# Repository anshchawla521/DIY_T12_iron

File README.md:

# DIY_T12_iron  

This repository conatins all the files for the DIY soldering iron which is compatible with hakko 936 style station and is meant to be used as the replacement PCB for HAKKO 936 style clones. This can support HAKKO T12 irons, HAKKO A1560(hakko 936 station) style irons as well as JBC c245 iron(yet to be checked).  

## Images

## Schematic  

## Code

The original Code was written by [HomeMade Projects](https://www.youtube.com/watch?v=tIUbGNTiDyI). Later i modified it to work with the provided PCB + support for more types of Iron's  

## What did i Learn ?

I learnt that most of the iron's use a triac and are AC powere or if they are DC work only upto 24V because making mosfets work/switch 60V is very hard

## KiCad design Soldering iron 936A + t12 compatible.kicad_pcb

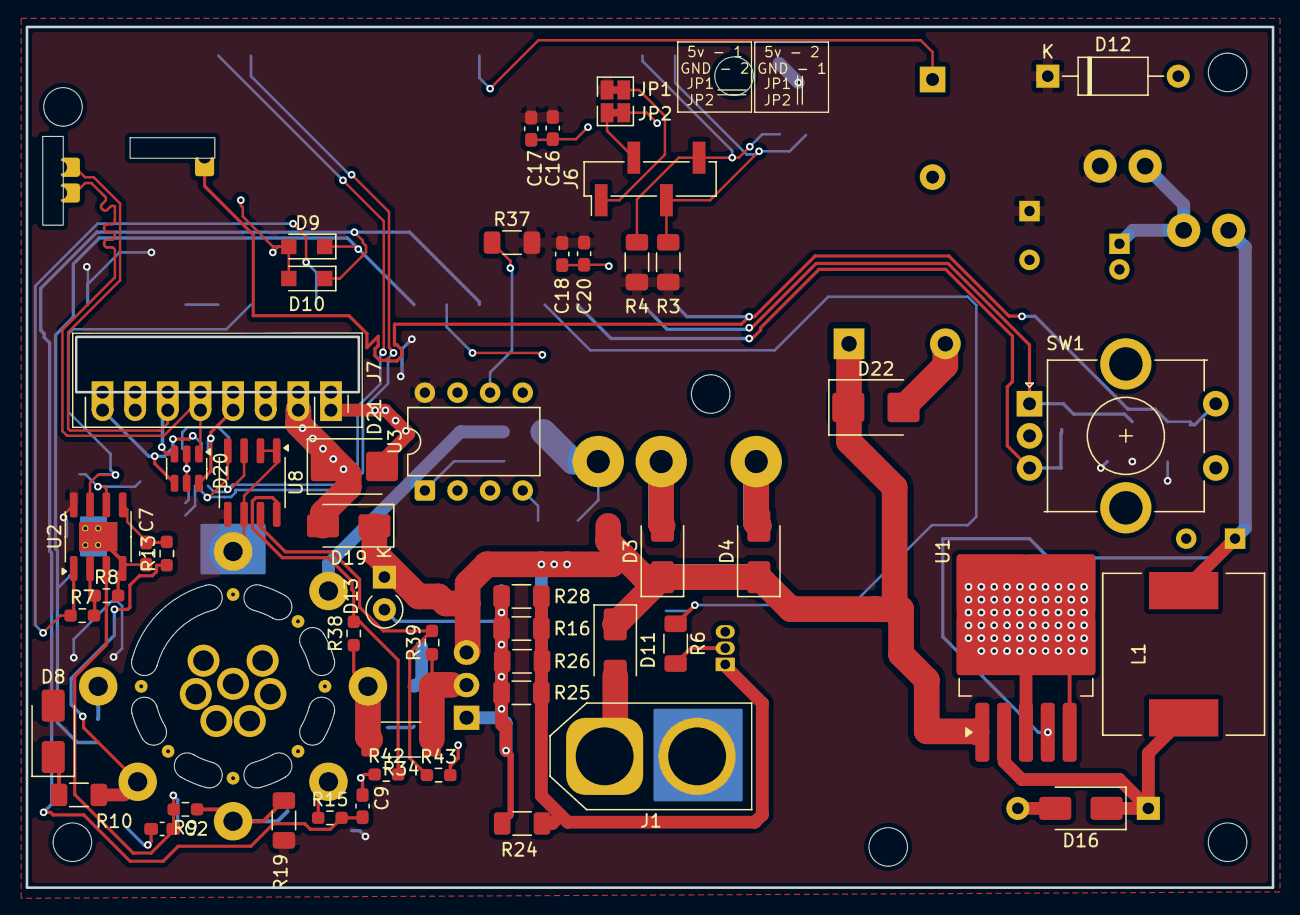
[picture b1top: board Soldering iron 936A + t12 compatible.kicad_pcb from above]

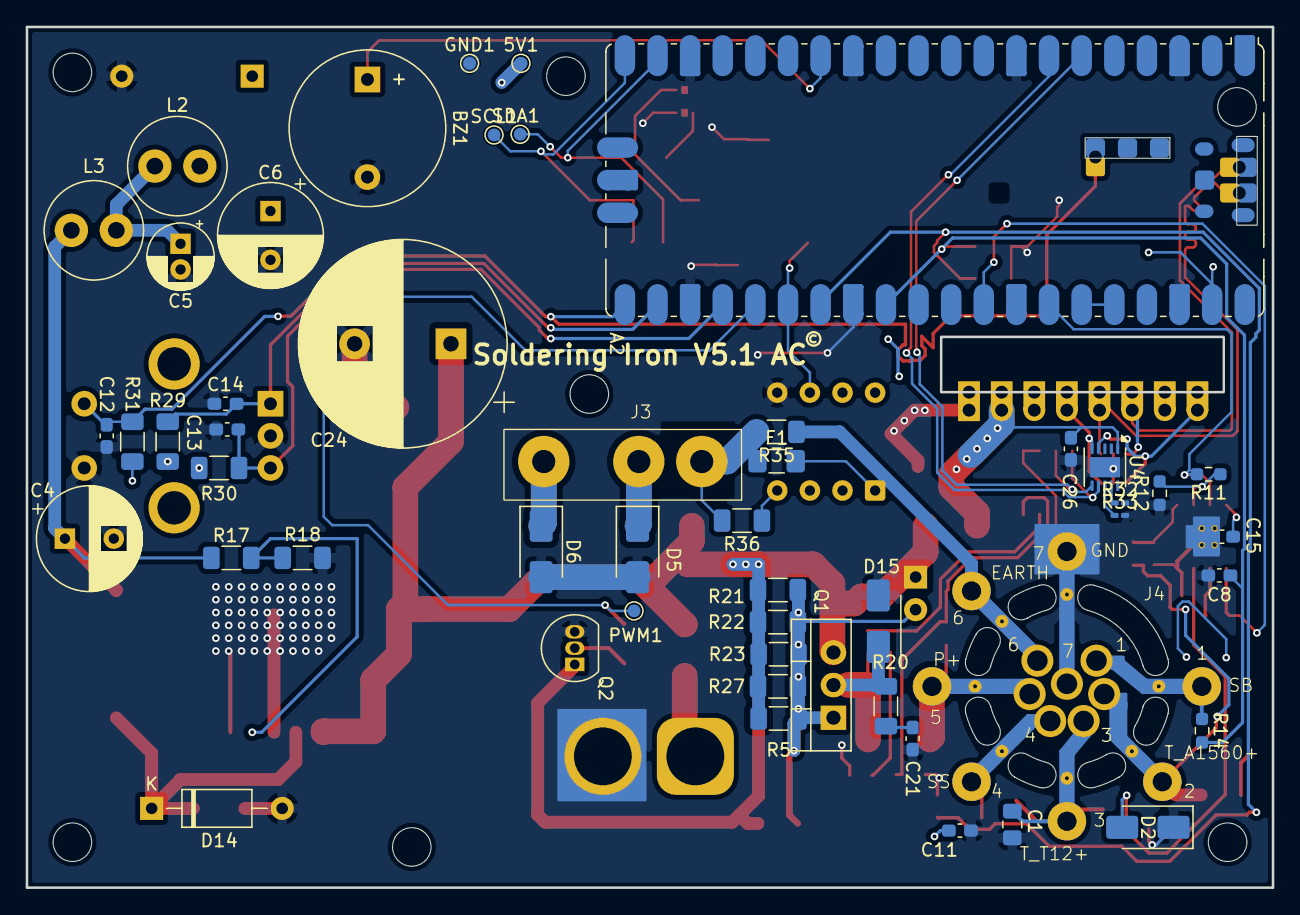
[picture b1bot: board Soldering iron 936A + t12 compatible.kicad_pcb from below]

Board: 2 copper layers, 97.0 x 67.0 mm, 103 parts (51 on the bottom side), 54 nets.

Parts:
5V1: TestPoint; TestPoint_Pad_D1.0mm
A2: RaspberryPi_Pico; RaspberryPi_Pico_SMD
BZ1: Buzzer; Buzzer_12x9.5RM7.6
C1: 0.47uf; C_0805_2012Metric_Pad1.18x1.45mm_HandSolder
C2, C7: 2nf; C_0603_1608Metric_Pad1.08x0.95mm_HandSolder
C4, C6: 220uf; CP_Radial_D8.0mm_P3.80mm
C5: 4.7uF; CP_Radial_D5.0mm_P2.00mm
C8, C9, C11, C12, C13, C14, C15, C16, C17, C18, C20, C21: 100nf; C_0603_1608Metric_Pad1.08x0.95mm_HandSolder
C24: 1000uF; CP_Radial_D16.0mm_P7.50mm
C26: 1uF; C_0603_1608Metric_Pad1.08x0.95mm_HandSolder
D2, D3, D4, D5, D6, D8, D11, D15, D16, D19: SS310; D_SMA
D9, D10: 3.3; Nexperia_CFP3_SOD-123W
D12: 3.3V; D_A-405_P10.16mm_Horizontal
D13: 18V; D_A-405_P2.54mm_Vertical_KathodeUp
D14: 1N5822; D_A-405_P10.16mm_Horizontal
D20: ESDA6V1-5SC6; SOT-23-6
D21: SMBJ24A; D_SMB
D22: SMBJ45A; D_SMB
F1: Fuse; Fuse_1206_3216Metric_Pad1.42x1.75mm_HandSolder
GND1: TestPoint; TestPoint_Pad_D1.0mm
J1: DC INPUT; AMASS_XT60-F_1x02_P7.20mm_Vertical
J3: AC input; BY-G4
J4: output_connector; aviaion_connector
J6: OLED; PinHeader_1x04_P2.54mm_Vertical_SMD_Pin1Left
J7: USB C BREAKOUT BOARD; PinHeader_1x08_P2.54mm_Vertical
JP1, JP2: SolderJumper_2_Bridged; SolderJumper-2_P1.3mm_Bridged_Pad1.0x1.5mm
L1: 33uH; L_12x12mm_H6mm
L2, L3: 100uH; L_Radial_D7.5mm_P3.50mm_Fastron_07P
PWM1: TestPoint; TestPoint_Pad_D1.0mm
Q1: IRF9540N; TO-220-3_Vertical
Q2: BC547; TO-92_Inline
R3, R4, R29, R30, R31, R37: 10k; R_1206_3216Metric_Pad1.30x1.75mm_HandSolder
R5, R21, R22, R23, R27: 1.5k; R_1206_3216Metric_Pad1.30x1.75mm_HandSolder
R6: 2k; R_1206_3216Metric_Pad1.30x1.75mm_HandSolder
R7: 220k; R_0603_1608Metric_Pad0.98x0.95mm_HandSolder
R8, R11, R12: 1k; R_0603_1608Metric_Pad0.98x0.95mm_HandSolder
R9, R13, R14, R15, R38, R39, R42, R43: 10k; R_0603_1608Metric_Pad0.98x0.95mm_HandSolder
R10: 470; R_1206_3216Metric_Pad1.30x1.75mm_HandSolder
R16, R24, R25, R26, R28: 3.3k; R_1206_3216Metric_Pad1.30x1.75mm_HandSolder
R17: 1.7k; R_1206_3216Metric_Pad1.30x1.75mm_HandSolder
R18: 1k; R_1206_3216Metric_Pad1.30x1.75mm_HandSolder
R19: 7.5M; R_1206_3216Metric_Pad1.30x1.75mm_HandSolder
R20: 100; R_1206_3216Metric_Pad1.30x1.75mm_HandSolder
R32: 22.6K; R_0201_0603Metric_Pad0.64x0.40mm_HandSolder
R33: 10k; R_0201_0603Metric_Pad0.64x0.40mm_HandSolder
R34: 0.1; R_2010_5025Metric_Pad1.40x2.65mm_HandSolder
R35: 1M; R_1206_3216Metric_Pad1.30x1.75mm_HandSolder
R36: 50K; R_1206_3216Metric_Pad1.30x1.75mm_HandSolder
SCL1: TestPoint; TestPoint_Pad_D1.0mm
SDA1: TestPoint; TestPoint_Pad_D1.0mm
SW1: RotaryEncoder_Switch; RotaryEncoder_Alps_EC11E-Switch_Vertical_H20mm_CircularMoun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
U1: LM2596S-ADJ; TO-263-5_TabPin3
U2: LM358; SOIC-8-1EP_3.9x4.9mm_P1.27mm_EP2.29x3mm_ThermalVias
U3: HCPL-3700; DIP-8_W7.62mm
U4: HUSB238; DFN-10-1EP_3x3mm_P0.5mm_EP1.58x2.35mm
U8: INA219AxD; SOIC-8_3.9x4.9mm_P1.27mm

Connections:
+3.3V: 5V1.1, A2.39 (VSYS), C6.1, C11.2, C15.1, C16.1, C17.1, C18.1, C20.1, D8.2 (A), D12.1 (K), JP1.1 (A), L2.2, R3.2, R4.2, R19.2, R29.1, R30.1, R31.2, R37.2, U2.8 (V+), U3.8 (VCC), U8.5 (VS)
+3V3: A2.35 (ADC_VREF), A2.36 (3V3)
/3.3v_unfiltered: C4.1, L1.2, L3.1, R17.2
/BUZZER: A2.14 (GPIO10), BZ1.1 (+)
/CC1: D20.6 (IO5), J7.4 (CC1), U4.5 (CC2)
/CC2: D20.4 (IO3), J7.8 (CC2), U4.4 (CC1)
/D+: A2.TP3 (USB_DP), D20.3 (IO2), J7.6 (D+)
/D-: A2.TP2 (USB_DM), D20.1 (IO1), J7.5 (D-)
/ENCODER A: A2.22 (GPIO17), C14.1, R29.2, SW1.A
/ENCODER B: A2.24 (GPIO18), C13.1, R30.2, SW1.B
/ENCODER S: A2.21 (GPIO16), A2.TP6 (~BOOTSEL), C12.1, R31.1, SW1.S2
/LEAK_ERR: A2.26 (GPIO20), R37.1, U3.6 (VO)
/MOS_OUT: D15.1 (K), Q1.2 (D), R20.1, R34.1, R39.1
/P+: J4.5, R34.2, R38.1
/PWM: A2.25 (GPIO19), PWM1.1, R6.1
/SCL: A2.7 (GPIO5), U4.7 (SCL), U8.4 (SCL)
/SCL1: A2.20 (GPIO15), J6.3 (GND), R3.1, SCL1.1
/SDA: A2.6 (GPIO4), U4.6 (SDA), U8.3 (SDA)
/SDA1: A2.19 (GPIO14), J6.4 (VDD), R4.1, SDA1.1
/VIN: C24.1, D3.1 (K), D4.1 (K), D11.1 (K), D13.1 (K), D19.1 (K), D22.1 (A1), Q1.3 (S), R5.1, R21.1, R22.1, R23.1, R27.1, U1.1 (VIN)
/VIN_USBC: C26.1, D19.2 (A), D21.1 (A1), J7.2 (VBUS), U4.1 (V_{DD})
/switch_Boost: J4.1, R14.1
/switch_Boost_d: A2.29 (GPIO22), C8.1, D9.1 (K), R14.2
/switch_sleep: J4.4, R15.1
/switch_sleep_d: A2.27 (GPIO21), C9.1, D10.1 (K), R15.2
/temp_readback_1: A2.32 (GPIO27_ADC1), R7.1, U2.1
/temp_readback_2: A2.34 (GPIO28_ADC2), R11.2, U2.7
/thermocouple_a1560 +: J4.2, R10.1, R13.1
/thermocouple_t12 +: C1.1, J4.3, R9.1, R19.1
Earth: F1.1, J3.1, R35.2, R36.2
GND: A2.3 (GND), A2.8 (GND), A2.13 (GND), A2.18 (GND), A2.23 (GND), A2.28 (GND), A2.38 (GND), A2.D2 (GND), BZ1.2 (-), C1.2, C2.2, C4.2, C5.2, C6.2, C7.2, C8.2, C9.2, C11.1, C12.2, C13.2, C14.2, C15.2, C16.2, C17.2, C18.2, C20.2, C21.2, C24.2, C26.2, D2.1 (K), D5.2 (A), D6.2 (A), D9.2 (A), D10.2 (A), D12.2 (A), D14.2 (A), D15.2 (A), D16.2 (A), D20.2 (GND), D20.5 (IO4), D21.2 (A2), D22.2 (A2), GND1.1, J1.2, J4.7, J7.1 (GND), JP2.1 (A), Q2.3 (E), R8.2, R12.1, R18.2, R32.2, R33.2, R42.1, R43.2, SW1.C, SW1.S1, U1.3 (GND), U1.5 (~ON/OFF), U2.4 (V-), U2.9 (thermal_pad), U3.5 (GND), U4.11 (GND), U8.1 (A1), U8.2 (A0), U8.6 (GND)
unnamed: C5.1, L2.1, L3.2
unnamed: C21.1, R20.2
unnamed: C2.1, D2.2 (A), R9.2, U2.3 (+)
unnamed: D3.2 (A), D5.1 (K), J3.2
unnamed: D4.2 (A), D6.1 (K), J3.3
unnamed: D8.1 (K), R10.2
unnamed: D11.2 (A), J1.1
unnamed: D13.2 (A), Q1.1 (G), R5.2, R16.2, R21.2, R22.2, R23.2, R24.2, R25.2, R26.2, R27.2, R28.2
unnamed: D14.1 (K), D16.1 (K), L1.1, U1.2 (OUT)
unnamed: F1.2, J4.6, R35.1, U3.1 (AC)
unnamed: J6.2 (SCL), JP2.2 (B)
unnamed: J6.1 (SDA), JP1.2 (B)
unnamed: Q2.2 (B), R6.2
unnamed: Q2.1 (C), R16.1, R24.1, R25.1, R26.1, R28.1
unnamed: R36.1, U3.4 (AC)
unnamed: R17.1, R18.1, U1.4 (FB)
unnamed: R7.2, R8.1, U2.2 (-)
unnamed: C7.1, R13.2, U2.5 (+)
unnamed: R11.1, R12.2, U2.6 (-)
unnamed: R32.1, U4.9 (ISET)
unnamed: R33.1, U4.8 (Vset)
unnamed: R38.2, R42.2, U8.8 (IN+)
unnamed: R39.2, R43.1, U8.7 (IN-)

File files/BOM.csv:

"Reference","Value","Description","Qty"
"5V1,GND1,PWM1,SCL1,SDA1,VBUS1","TestPoint","test point","6"
"A1","Arduino_Nano_v2.x","Arduino Nano v2.x","1"
"BZ1","Buzzer","Buzzer, polarized","1"
"C1","0.47uf","Polarized capacitor","1"
"C2,C7","2nf","Unpolarized capacitor","2"
"C4,C6","220uf","Polarized capacitor","2"
"C5","4.7uF","Polarized capacitor","1"
"C8,C9,C10,C11,C12,C13,C14,C15,C16,C17,C18,C20,C21,C23,C25,C27,C28","100nf","Unpolarized capacitor","17"
"C19,C24","1000uF","Polarized capacitor","2"
"C22","1nf","Unpolarized capacitor","1"
"C26","1uF","Unpolarized capacitor","1"
"D1,D9,D10,D12","5V","Zener diode","4"
"D2,D3,D4,D5,D6,D7,D8,D11,D15,D16,D17,D18,D19","SS310","100V 3A Schottky Diode, SMA","13"
"D13","18V","Zener diode","1"
"D14","1N5822","40V 3A Schottky Barrier Rectifier Diode, DO-201AD","1"
"D20","ESDA6V1-5SC6","Quintuple bidirectional transil, Suppressor for ESD protection, 6V1 Breakdown, SOT-23-6","1"
"D21","SMBJ24A","600W unidirectional Transil Transient Voltage Suppressor, 6.8Vrwm, DO-214AA","1"
"D22","SMBJ45A","600W unidirectional Transil Transient Voltage Suppressor, 6.8Vrwm, DO-214AA","1"
"F1","Fuse","Fuse 1A 1206","1"
"J1","DC INPUT","Generic connector, single row, 01x02, script generated","1"
"J2","USB TO SERIAL","Generic connector, single row, 01x04, script generated","1"
"J3","AC input","Generic connector, single row, 01x03, script generated","1"
"J4","output_connector","Generic connector, single row, 01x07, script generated","1"
"J5","mosfet_driver_future_backup","Generic connector, single row, 01x06, script generated","1"
"J6","OLED","Generic connector, single row, 01x04, script generated","1"
"J7","USB C BREAKOUT BOARD","Generic connector, single row, 01x08, script generated","1"
"J8,J10,J11","Conn_01x01_Socket","Generic connector, single row, 01x01, script generated","3"
"JP1,JP2","SolderJumper_2_Bridged","Solder Jumper, 2-pole, closed/bridged","2"
"L1","33uH","Inductor","1"
"L2,L3","100uH","Inductor","2"
"Q1","IRF9540N","-23A Id, -100V Vds, 117mOhm Rds, P-Channel HEXFET Power MOSFET, TO-220","1"
"Q2","BC547","0.1A Ic, 45V Vce, Small Signal NPN Transistor, TO-92","1"
"R1,R3,R4,R9,R13,R14,R15,R29,R30,R31,R33,R37","10k","Resistor","12"
"R2","100k","Resistor","1"
"R5,R21,R22,R23,R27","1.5k","Resistor","5"
"R6","2k","Resistor","1"
"R7","220k","Resistor","1"
"R8,R11,R12,R18","1k","Resistor","4"
"R10","470","Resistor","1"
"R16,R24,R25,R26,R28","3.3k","Resistor","5"
"R17","3k","Resistor","1"
"R19","7.5M","Resistor","1"
"R20","100","Resistor","1"
"R32","22.6K","Resistor","1"
"R34,R38","5.1K","Resistor","2"
"R35","1M","Resistor","1"
"R36","50K","Resistor","1"
"SW1","RotaryEncoder_Switch","Rotary encoder, dual channel, incremental quadrate outputs, with switch","1"
"U1","LM2596S-ADJ","Adjustable 3A Step-Down Voltage Regulator, TO-263","1"
"U2","LM358","Low-Power, Dual Operational Amplifiers, DIP-8/SOIC-8/TO-99-8","1"
"U3","ACS712xLCTR-05B","±5A Bidirectional Hall-Effect Current Sensor, +5.0V supply, 185mV/A, SOIC-8","1"
"U4","HUSB238","USB C PD CONTROLER","1"
"U5","PC817","DC Optocoupler, Vce 35V, CTR 50-300%, DIP-4","1"
"U6","REF3040","4.096V 50-ppm/°C Max, 50-μA, CMOS Voltage Reference, SOT-23-3","1"

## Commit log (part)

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2025-05-25 second commit
2025-06-23 PCB arrived , T12 verified , code updating , Fixed mistakes and redid schmatic
2025-06-23 added BOM generation + decoupling Cap for other orination of OLED , Fixed PCB orientation in Readme
2025-07-01 Updated schematic but have to update layout , foot prints ,add mosfet driver for 31 KHZ driving
2025-07-05 Schematic finalised -> will do layout next
2025-07-05 Added all 3d models
2025-07-07 added all 3d model files , almost finalised schematic , rough placment of big components
2025-07-12 Finalised schematic , placement
2025-07-13 Almost completed layout , checks pending
2025-07-13 Layout fully complete yet to be reviewed
2025-07-14 Review 5V and GND planes
2025-07-14 Checked all errors , fixed whatever was possible only clearance error's exist , now have to check warnings
2025-07-14 Added , placed refernce , next have to check warnings , silkscreen
2025-07-14 Review few of the warnings
2025-07-15 only warnings are left to see , will now try slots cutting for type c
2025-07-15 Added cut for the type C board , differential roting pending
2025-07-15 Length matched the usb data traces
2025-07-15 widened the slots
2025-07-15 Centralised the connector and screen
2025-07-17 added ESD diodes
2025-07-19 added esd , oled support headers , oled switchable pinout
2025-07-21 sent for FAB , case also designed, lets hope for best
2025-08-24 Added castellated edges
2025-09-16 added relative path + generated files
2025-09-16 updated foot print of gx 16 connector
2026-02-20 Separated Aux Power and Output into different files
2026-05-08 final schematic and layout done need to review though , removed uneccesary features
